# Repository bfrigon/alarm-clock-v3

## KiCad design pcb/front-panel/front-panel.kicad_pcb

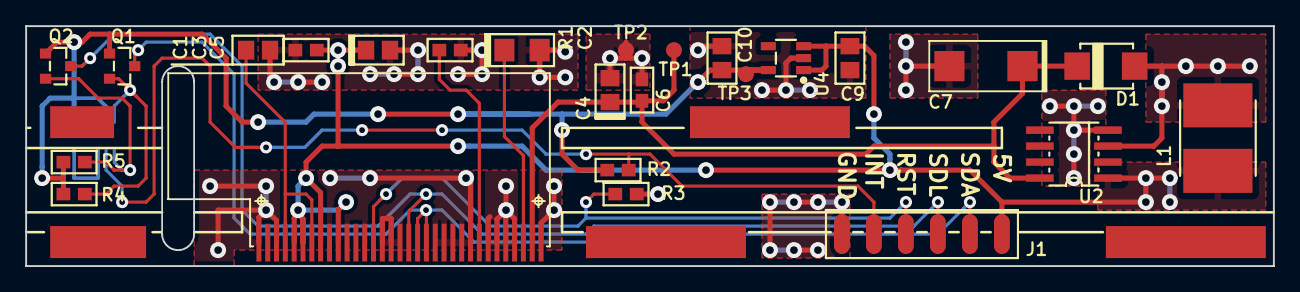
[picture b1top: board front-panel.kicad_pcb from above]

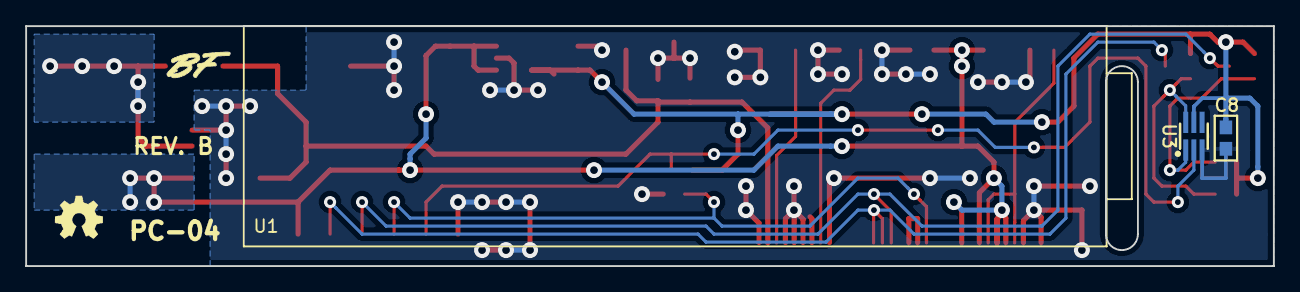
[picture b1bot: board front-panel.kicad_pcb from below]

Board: 2 copper layers, 99.1 x 19.0 mm, 32 parts (3 on the bottom side), 14 nets.

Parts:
C1, C9: 1uF; C-0805
C2: 4.7uF; CPL-1206
C3, C6, C8: 100nF; C-0603
C4: 10uF; CPL-0805
C5: 4.7uF; CPL-0805
C7: 22uF; CPL-2312
C10: 3.3uF; C-0805
D1: MBRS120T3; DO-214-AA
H1, H2, H3: HEADER-1x01; SolderPad-100x500
H4: HEADER-1x01; SolderPad-100x300
H5: HEADER-1x01; SolderPad-100x200
J1: HEADER-1x06; WP-50mil-1x06
L1: 33uH; IND-CD54
Q1, Q2: BSS138; SOT23
R1: 500k; R-0603
R2, R3: 10k; R-0603
R4, R5: 4.7k; R-0603
TP1: 12V; TEST-POINT-50
TP2: GND; TEST-POINT-50
TP3: 3.3V; TEST-POINT-50
U1: ER-OLED1602-4W; LCD-ER-OLED1602
U2: LT1109CS8-12; SOIC8
U3: TSL2591; DFN6
U4: LP2981-33DBVT; SOT23-5

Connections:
+3V3: C8.1, C10.2, Q1.1, Q2.1, R2.2, R4.2, R5.2, TP3.1, U3.5, U4.5
+5V: C3.2, C5.A, C9.2, J1.1, L1.1, U1.5, U1.6, U1.8, U1.10, U2.1, U4.1, U4.3
+12V: C4.A, C6.2, C7.A, D1.K, TP1.1, U1.32, U2.8
/INT: J1.5, R2.1, U3.2
/SCL: J1.3, Q2.3, U1.18
/SCL_3V3: Q2.2, R5.1, U3.1
/SDA: J1.2, Q1.3, U1.19, U1.20
/SDA_3V3: Q1.2, R4.1, U3.6
/SW_12V: D1.A, L1.2, U2.3
/~RESET: J1.4, R3.2, U1.14
GND: C1.1, C2.K, C3.1, C4.K, C5.K, C6.1, C7.K, C8.2, C9.1, C10.1, J1.6, R1.2, R3.1, TP2.1, U1.1, U1.3, U1.9, U1.11, U1.13, U1.15, U1.16, U1.17, U1.21, U1.22, U1.23, U1.24, U1.25, U1.27, U1.28, U1.29, U1.30, U1.33, U2.4, U3.3, U4.2
unnamed: C1.2, U1.4, U1.7
unnamed: C2.A, U1.31
unnamed: R1.1, U1.26

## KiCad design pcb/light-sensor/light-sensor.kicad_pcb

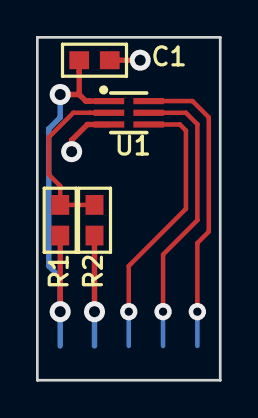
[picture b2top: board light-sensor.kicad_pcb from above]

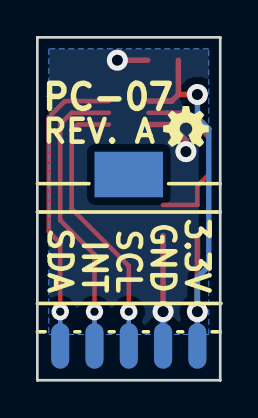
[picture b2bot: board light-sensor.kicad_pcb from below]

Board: 2 copper layers, 10.2 x 19.0 mm, 6 parts (2 on the bottom side), 6 nets.

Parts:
C1: 100nF; C-0603
J1: HEADER-1x05; WP-40mil-1x05
J2: HEADER-1x01; SolderPad-100x150
R1, R2: DNP; R-0603
U1: TSL2561; DFN6

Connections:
+3V3: C1.1, J1.1, R1.2, U1.1
/INT: J1.4, U1.5
/SCL_3V3: J1.3, U1.4
/SDA_3V3: J1.5, U1.6
GND: C1.2, J1.2, R2.1, U1.3
unnamed: R1.1, R2.2, U1.2

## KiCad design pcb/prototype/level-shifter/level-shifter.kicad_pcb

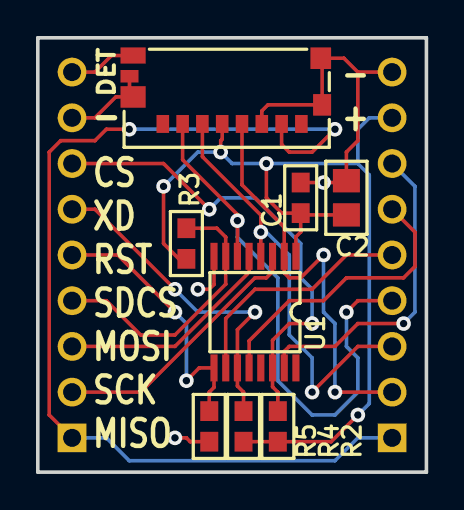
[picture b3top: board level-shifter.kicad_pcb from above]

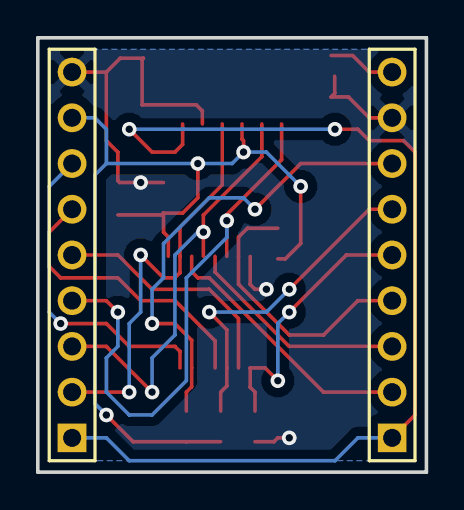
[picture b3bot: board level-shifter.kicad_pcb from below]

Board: 2 copper layers, 21.6 x 24.1 mm, 10 parts (2 on the bottom side), 16 nets.

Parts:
C1: 100nF; C-0603
C2: 10uF; C-0805
J1, J3: HEADER-1x09; HDR-M-1x09
J2: Micro_SD; MOLEX-MICROSD-475710001
R2, R3, R4, R5: 100k; R-0603
U1: 74HC4050DB; TSSOP16

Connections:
/CCS: J1.7, R2.2, U1.14
/CCS_3V3: J3.7, U1.15
/CMOSI_3V3: J2.3, J3.3, U1.4
/CRST: J1.5, R5.2, U1.9
/CRST_3V3: J3.5, U1.10
/CSCK_3V3: J2.5, J3.2, U1.2
/MISO: J1.1, J2.7, J3.1
/MOSI: J1.3, U1.5
/SCK: J1.2, U1.3
/SDCS: J1.4, R3.2, U1.7
/SDCS_3V3: J2.2, J3.4, U1.6
/SD_DET: J1.9, J2.DT
/XDCS: J1.6, R4.2, U1.11
/XDCS_3V3: J3.6, U1.12
DVDD: C1.2, C2.2, J2.4, J3.8, R2.1, R3.1, R4.1, U1.1
GND: C1.1, C2.1, J1.8, J2.6, J2.DC, J2.SH, J3.9, R5.1, U1.8
